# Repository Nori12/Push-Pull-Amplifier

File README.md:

# Push-Pull-Amplifier
Cadsoft Eagle Project

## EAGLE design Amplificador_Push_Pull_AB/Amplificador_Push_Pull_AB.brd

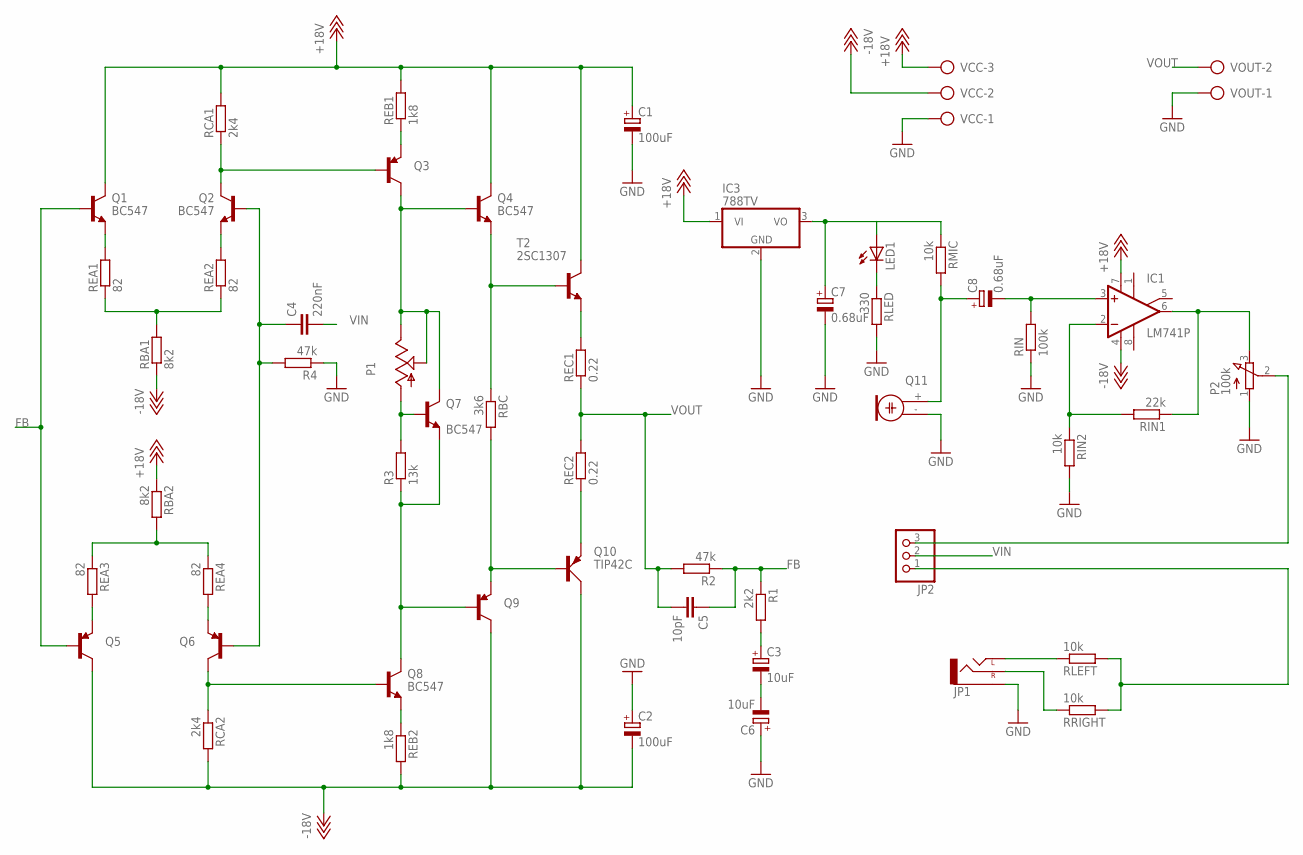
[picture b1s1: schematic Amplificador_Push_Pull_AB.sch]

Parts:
C1, C2: 100uF; E2,5-6
C3, C6: 10uF; E2,5-5
C4: 220nF; C025-025X050
C5: 10pF; C025-025X050
C7, C8: 0.68uF; E2,5-5
IC1: LM741P; DIL08
IC3: 788TV; TO220V
JP1: AUDIO-JACKPTH; AUDIO-JACK
JP2: PINHD-1X3; 1X03
LED1: LED5MM
P1: TRIM_US-S64W; S64W
P2: 100k; 3RP/1610N
Q1, Q2, Q4, Q7, Q8: BC547; TO92
Q3, Q5, Q6, Q9: TRANSISTOR_PNPTO92; TO-92
Q10: TIP42C; TO220AV
Q11: ELECTRET; 9.7ELECTRET
R1: 2k2; 0207/10
R2, R4: 47k; 0207/10
R3: 13k; 0207/10
RBA1, RBA2: 8k2; 0207/10
RBC: 3k6; 0207/10
RCA1, RCA2: 2k4; 0207/10
REA1, REA2, REA3, REA4: 82; 0207/10
REB1, REB2: 1k8; 0207/10
REC1, REC2: 0.22; 0617/22
RIN: 100k; 0207/7
RIN1: 22k; 0207/7
RIN2: 10k; 0207/10
RLED: 330; 0207/7
RLEFT: 10k; 0207/7
RMIC: 10k; 0207/7
RRIGHT: 10k; 0207/7
T2: 2SC1307; TO220AV
VCC: AK500/3-H
VOUT: AK500/2-H

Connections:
+5V: C7.+, IC3.3 (VO), LED1.A, RMIC.1
+18V: C1.+, IC1.7 (V+), IC3.1 (VI), Q1.3 (C), Q4.3 (C), RBA2.1, RCA1.2, REB1.2, T2.2 (C), VCC.3
-18V: C2.-, IC1.4 (V-), Q5.1 (C), Q9.1 (C), Q10.C, RBA1.1, RCA2.2, REB2.2, VCC.2
FB: C5.1, Q1.2 (B), Q5.2 (B), R1.1, R2.1
GND: C1.-, C2.+, C6.+, C7.-, IC3.2 (GND), JP1.SLEEVE, P2.1 (A), Q11.- (1), R4.1, RIN.1, RIN2.2, RLED.2, VCC.1, VOUT.1
HEHEAH: C4.1, Q2.2 (B), Q6.2 (B), R4.2
unnamed: Q1.1 (E), REA1.2
unnamed: RBA1.2, REA1.1, REA2.1
unnamed: RBA2.2, REA3.1, REA4.1
unnamed: Q2.1 (E), REA2.2
unnamed: Q2.3 (C), Q3.2 (B), RCA1.1
unnamed: Q6.3 (E), REA4.2
unnamed: Q5.3 (E), REA3.2
unnamed: Q6.1 (C), Q8.2 (B), RCA2.1
unnamed: C8.+, Q11.+ (2), RMIC.2
unnamed: Q3.3 (E), REB1.1
unnamed: P1.E, P1.S, Q3.1 (C), Q4.2 (B), Q7.3 (C)
unnamed: JP1.RING (RIGHT), RRIGHT.1
unnamed: Q4.1 (E), RBC.1, T2.1 (B)
unnamed: JP1.TIP (LEFT), RLEFT.1
unnamed: Q7.1 (E), Q8.3 (C), Q9.2 (B), R3.1
unnamed: Q8.1 (E), REB2.1
unnamed: Q9.3 (E), Q10.B, RBC.2
unnamed: LED1.K (C), RLED.1
unnamed: REC1.2, T2.3 (E)
unnamed: JP2.1, RLEFT.2, RRIGHT.2
unnamed: Q10.E, REC2.1
unnamed: C3.-, C6.-
unnamed: C3.+, R1.2
unnamed: C8.-, IC1.3 (+IN), RIN.2
unnamed: IC1.2 (-IN), RIN1.2, RIN2.1
unnamed: IC1.6 (OUT), P2.3 (E), RIN1.1
unnamed: JP2.3, P2.2 (S)
P1: P1.A, Q7.2 (B), R3.2
VIN: C4.2, JP2.2
VOUT: C5.2, R2.2, REC1.1, REC2.2, VOUT.2

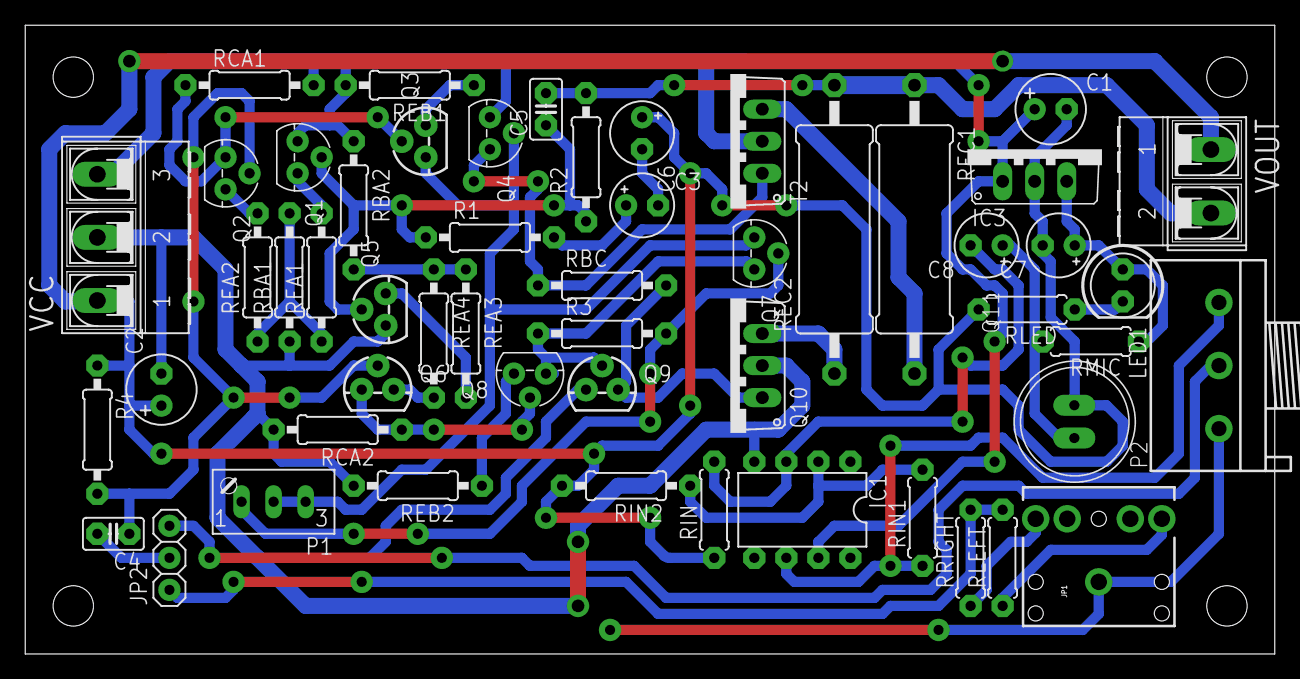
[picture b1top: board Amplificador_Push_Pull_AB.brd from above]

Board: 2 copper layers, 99.0 x 49.8 mm, 53 parts (0 on the bottom side), 36 nets.

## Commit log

2017-06-15 Name modified
2017-06-15 Schematic done. Working on board.
2017-06-15 One connection left.
2017-06-15 Board finished. Need to verify.
2017-06-16 Ajustments done. Continue the need for verifying.
2017-06-16 Error found and corrected.
2017-06-16 Separate fround line done. Its resistance is approximately 0.1 ohm. Schematic connections integrity verified. Check DRC next time!
2017-06-16 Led added on schematic. Need to put allocate it in board now.
2017-06-16 Separete ground line with polygon done. LED and its resistor added.
2017-06-16 Useless file deleted.
2017-06-16 Wrong positioned jumper reallocated.
2017-06-16 Pads and vias increased outer diameter.
2017-06-16 Double connection with jumper and resistor in one pad solved. Printable file genererated. Ready!!!
2017-06-28 Inversed polarity capactitor problem solved. Simulation files added. PCB assembled and worked good! Next time: Limit the outputs's maximum voltage of the op. amp. through a smaller gain or decrease t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
2017-06-28 Useless files deleted.

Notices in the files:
parts and their libraries:
SparkFun-DiscreteSemi: Licensing: Creative Commons ShareAlike 4.0 International - https://creativecommons.org/licenses/by-sa/4.0
